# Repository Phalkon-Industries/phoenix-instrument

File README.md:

Git repo for the content of the new Phoenix ph handheld instrument.

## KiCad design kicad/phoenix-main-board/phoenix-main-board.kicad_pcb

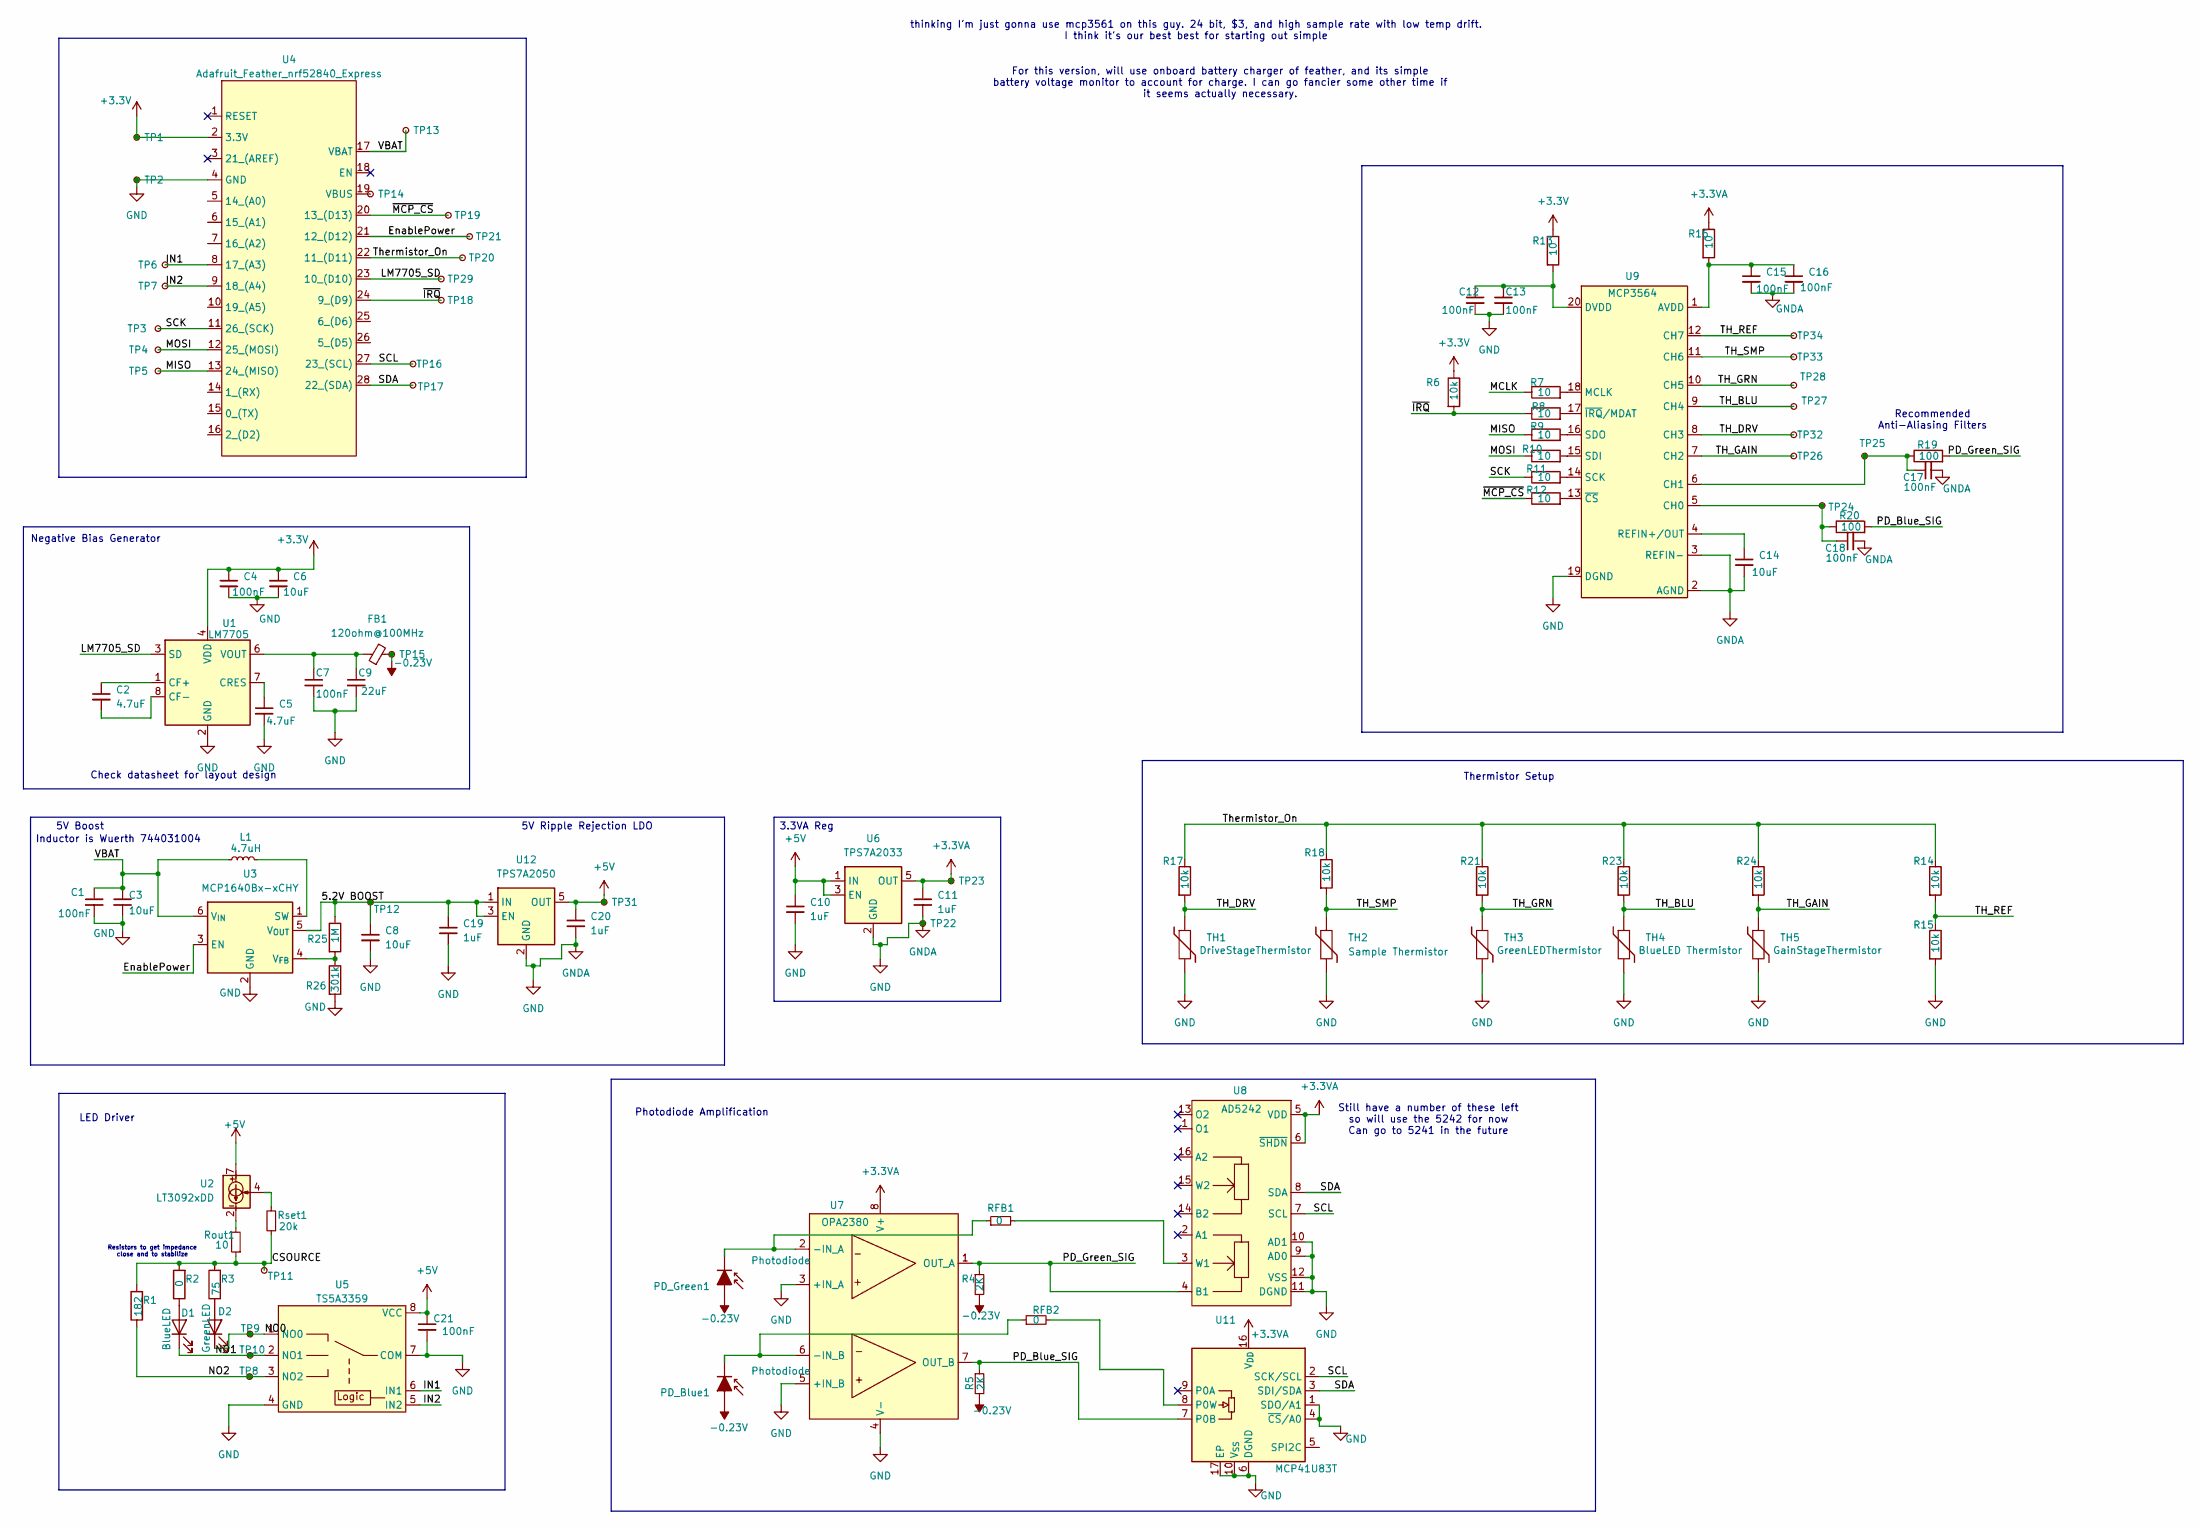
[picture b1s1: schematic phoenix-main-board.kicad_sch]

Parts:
C1, C4, C7, C12, C13, C15, C16, C17, C18, C21: 100nF; C_0603_1608Metric
C2, C5: 4.7uF; C_0603_1608Metric
C3, C6, C8, C14: 10uF; C_0603_1608Metric
C9: 22uF; C_0603_1608Metric
C10, C11, C19, C20: 1uF; C_0603_1608Metric
D1: BlueLED; LED_D5.0mm_Horizontal_O1.27mm_Z3.0mm
D2: GreenLED; LED_D5.0mm_Horizontal_O1.27mm_Z3.0mm
FB1: 120ohm@100MHz; R_0603_1608Metric
L1: 4.7uH; L_Wuerth_WE-TPC-3816
PD_Blue1: Photodiode; PD_Vertical
PD_Green1: Photodiode; PD_Vertical
R1: 182; R_0603_1608Metric
R2: 0; R_0603_1608Metric
R3: 75; R_0603_1608Metric
R4, R5: 2K; R_0603_1608Metric
R6, R14, R15, R17, R18, R21, R23, R24: 10k; R_0603_1608Metric
R7, R8, R9, R10, R11, R12, R13, R16: 10; R_0603_1608Metric
R19, R20: 100; R_0603_1608Metric
R25: 1M; R_0603_1608Metric
R26: 301k; R_0603_1608Metric
RFB1, RFB2: 0; R_0603_1608Metric
Rout1: 10; R_0603_1608Metric
Rset1: 20k; R_0603_1608Metric
TH1: DriveStageThermistor; R_0603_1608Metric
TH2: Sample Thermistor; ThermistorWire
TH3: GreenLEDThermistor; ThermistorWire
TH4: BlueLED Thermistor; ThermistorWire
TH5: GainStageThermistor; R_0603_1608Metric
TP1, TP2, TP3, TP4, TP5, TP6, TP7, TP8, TP9, TP10, TP11, TP12, TP13, TP14, TP15, TP16, TP17, TP18, TP19, TP20, TP21, TP22, TP23, TP24, TP25, TP26, TP27, TP28, TP29, TP31, TP32, TP33, TP34: TestPoint_Small; TestPoint_Keystone_5000-5004_Miniature
U1: LM7705; VSSOP-8_3x3mm_P0.65mm
U2: LT3092xDD; DFN-8-1EP_3x3mm_P0.5mm_EP1.66x2.38mm
U3: MCP1640Bx-xCHY; SOT-23-6
U4: Adafruit_Feather_nrf52840_Express; Adafruit Feather nrf52840 Express
U5: TS5A3359; VSSOP-8_2.3x2mm_P0.5mm
U6: TPS7A2033; SOT-23-5
U7: OPA2380; MSOP-8_3x3mm_P0.65mm
U8: AD5242; TSSOP-16_4.4x5mm_P0.65mm
U9: MCP3564; TSSOP-20_4.4x6.5mm_P0.65mm
U11: MCP41U83T; Texas_RSA_VQFN-16-1EP_4x4mm_P0.65mm_EP2.7x2.7mm
U12: TPS7A2050; SOT-23-5

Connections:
+3.3V: C4.1, C6.1, R6.1, R13.1, TP1.1, U1.4 (VDD), U4.2 (3.3V)
+3.3VA: C11.1, R16.1, TP23.1, U6.5 (OUT), U7.8 (V+), U8.5 (VDD), U8.6 (~SHDN), U11.16 (V_{DD})
+5V: C10.1, C20.1, C21.1, TP31.1, U2.7, U2.8, U5.8 (VCC), U6.1 (IN), U6.3 (EN), U12.5 (OUT)
-0.23V: FB1.2, PD_Blue1.2 (A), PD_Green1.2 (A), R4.2, R5.2, TP15.1
/5.2V BOOST: C8.1, C19.1, R25.1, TP12.1, U3.5 (V_{OUT}), U12.1 (IN), U12.3 (EN)
/CSOURCE: R1.2, R2.2, R3.2, Rout1.1, Rset1.1, TP11.1
/EnablePower: TP21.1, U3.3 (EN), U4.21 (12_(D12))
/IN1: TP6.1, U4.8 (17_(A3)), U5.6 (IN1)
/IN2: TP7.1, U4.9 (18_(A4)), U5.5 (IN2)
/LM7705_SD: TP29.1, U1.3 (SD), U4.23 (10_(D10))
/MCLK: R7.1
/MISO: R9.1, TP5.1, U4.13 (24_(MISO))
/MOSI: R10.1, TP4.1, U4.12 (25_(MOSI))
/NO0: D2.1 (K), TP9.1, U5.1 (NO0)
/NO1: D1.1 (K), TP10.1, U5.2 (NO1)
/NO2: R1.1, TP8.1, U5.3 (NO2)
/PD_Blue_SIG: R5.1, R20.2, U7.7 (OUT_B), U11.7 (P0B)
/PD_Green_SIG: R4.1, R19.2, U7.1 (OUT_A), U8.4 (B1)
/SCK: R11.1, TP3.1, U4.11 (26_(SCK))
/SCL: TP16.1, U4.27 (23_(SCL)), U8.7 (SCL), U11.2 (SCK/SCL)
/SDA: TP17.1, U4.28 (22_(SDA)), U8.8 (SDA), U11.3 (SDI/SDA)
/TH_BLU: R23.2, TH4.1, TP27.1, U9.9 (CH4)
/TH_DRV: R17.2, TH1.1, TP32.1, U9.8 (CH3)
/TH_GAIN: R24.2, TH5.1, TP26.1, U9.7 (CH2)
/TH_GRN: R21.2, TH3.1, TP28.1, U9.10 (CH5)
/TH_REF: R14.2, R15.1, TP34.1, U9.12 (CH7)
/TH_SMP: R18.2, TH2.1, TP33.1, U9.11 (CH6)
/Thermistor_On: R14.1, R17.1, R18.1, R21.1, R23.1, R24.1, TP20.1, U4.22 (11_(D11))
/VBAT: C1.1, C3.1, L1.1, TP13.1, U3.6 (V_{IN}), U4.17 (VBAT)
/~IRQ: R6.2, R8.1, TP18.1, U4.24 (9_(D9))
/~MCP_CS: R12.1, TP19.1, U4.20 (13_(D13))
GND: C1.2, C3.2, C4.2, C5.2, C6.2, C7.2, C8.2, C9.2, C10.2, C11.2, C12.2, C13.2, C14.2, C15.2, C16.2, C17.2, C18.2, C19.2, C20.2, C21.2, R15.2, R26.2, TH1.2, TH2.2, TH3.2, TH4.2, TH5.2, TP2.1, TP22.1, U1.2 (GND), U1.5 (GND), U3.2 (GND), U4.4 (GND), U5.4 (GND), U5.7 (COM), U6.2 (GND), U7.3 (+IN_A), U7.4 (V-), U7.5 (+IN_B), U8.9 (AD0), U8.10 (AD1), U8.11 (DGND), U8.12 (VSS), U9.2 (AGND), U9.3 (REFIN-), U9.19 (DGND), U11.1 (SDO/A1), U11.4 (~CS/A0), U11.6 (DGND), U11.10 (V_{SS}), U11.17 (EP), U12.2 (GND)
unnamed: D1.2 (A), R2.1
unnamed: D2.2 (A), R3.1
unnamed: PD_Blue1.1 (K), RFB2.1, U7.6 (-IN_B)
unnamed: PD_Green1.1 (K), RFB1.1, U7.2 (-IN_A)
unnamed: Rout1.2, U2.1, U2.2, U2.9
unnamed: Rset1.2, U2.4
unnamed: C2.1, U1.1 (CF+)
unnamed: C2.2, U1.8 (CF-)
unnamed: C5.1, U1.7 (CRES)
unnamed: C7.1, C9.1, FB1.1, U1.6 (VOUT)
unnamed: L1.2, U3.1 (SW)
unnamed: R25.2, R26.1, U3.4 (V_{FB})
unnamed: TP14.1, U4.19 (VBUS)
unnamed: RFB1.2, U8.3 (W1)
unnamed: C15.1, C16.1, R16.2, U9.1 (AVDD)
unnamed: C18.1, R20.1, TP24.1, U9.5 (CH0)
unnamed: C17.1, R19.1, TP25.1, U9.6 (CH1)
unnamed: C12.1, C13.1, R13.2, U9.20 (DVDD)
unnamed: R7.2, U9.18 (MCLK)
unnamed: C14.1, U9.4 (REFIN+/OUT)
unnamed: R11.2, U9.14 (SCK)
unnamed: R10.2, U9.15 (SDI)
unnamed: R9.2, U9.16 (SDO)
unnamed: R12.2, U9.13 (~CS)
unnamed: R8.2, U9.17 (~IRQ/MDAT)
unnamed: RFB2.2, U11.8 (P0W)

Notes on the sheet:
Inductor is Wuerth 744031004
For this version, will use onboard battery charger of feather, and its simple battery voltage monitor to account for charge. I can go fancier some other time if it seems actually necessary.
Check datasheet for layout design
Photodiode Amplification
3.3VA Reg
Resistors to get impedance close and to stabilize
Recommended Anti-Aliasing Filters
thinking I'm just gonna use mcp3561 on this guy. 24 bit, $3, and high sample rate with low temp drift. I think it's our best best for starting out simple
LED Driver
5V Boost
Negative Bias Generator
Thermistor Setup
5V Ripple Rejection LDO
Still have a number of these left so will use the 5242 for now Can go to 5241 in the future

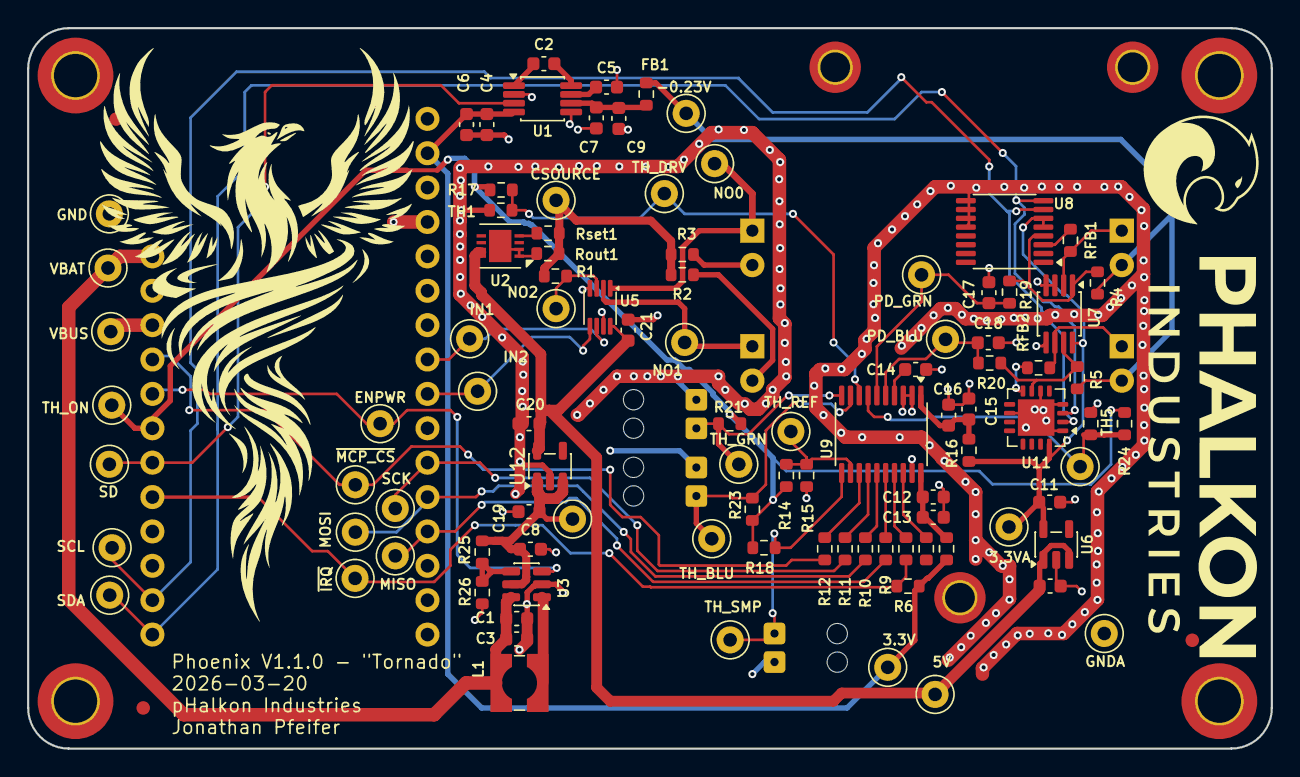
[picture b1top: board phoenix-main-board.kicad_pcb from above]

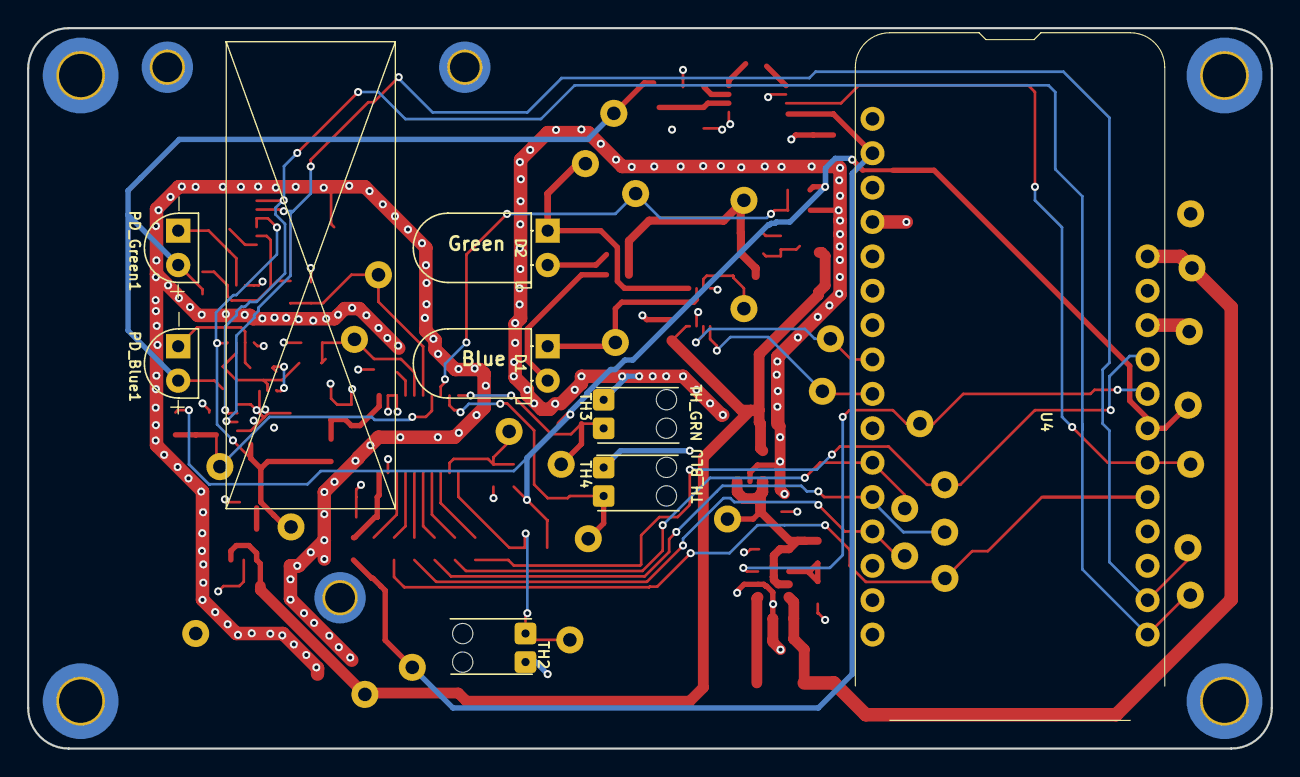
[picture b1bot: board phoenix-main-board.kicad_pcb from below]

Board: 4 copper layers, 91.9 x 53.2 mm, 108 parts (8 on the bottom side), 57 nets.

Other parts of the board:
FID1: Fiducial_1mm_Mask2mm
FID2, FID3: (no value)

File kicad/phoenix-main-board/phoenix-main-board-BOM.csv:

"Id";"Designator";"Footprint";"Quantity";"Designation";"Supplier and ref";
1;"TP25,TP11,TP31,TP7,TP2,TP16,TP23,TP22,TP9,TP33,TP14,TP15,TP5,TP3,TP1,TP26,TP34,TP10,TP4,TP19,TP18,TP32,TP29,TP27,TP17,TP20,TP8,TP24,TP6,TP12,TP28,TP21,TP13";"TestPoint_Keystone_5000-5004_Miniature";33;"TestPoint_Small";;;
2;"U11";"Texas_RSA_VQFN-16-1EP_4x4mm_P0.65mm_EP2.7x2.7mm";1;"MCP41U83T";;;
3;"R19,R20";"R_0603_1608Metric";2;"100";;;
4;"R7,R8,R10,R11,R12,Rout1,R13,R16,R9";"R_0603_1608Metric";9;"10";;;
5;"C12,C18,C7,C13,C16,C15,C21,C1,C17,C4";"C_0603_1608Metric";10;"100nF";;;
6;"C5,C2";"C_0603_1608Metric";2;"4.7uF";;;
7;"U1";"VSSOP-8_3x3mm_P0.65mm";1;"LM7705";;;
8;"U7";"MSOP-8_3x3mm_P0.65mm";1;"OPA2380";;;
9;"C6,C14,C8,C3";"C_0603_1608Metric";4;"10uF";;;
10;"FID3,FID2";"";2;"";;;
11;"R2,RFB2,RFB1";"R_0603_1608Metric";3;"0";;;
12;"Rset1";"R_0603_1608Metric";1;"20k";;;
13;"U2";"DFN-8-1EP_3x3mm_P0.5mm_EP1.66x2.38mm";1;"LT3092xDD";;;
14;"R5,R4";"R_0603_1608Metric";2;"2K";;;
15;"C9";"C_0603_1608Metric";1;"22uF";;;
16;"C11,C20,C10,C19";"C_0603_1608Metric";4;"1uF";;;
17;"U5";"VSSOP-8_2.3x2mm_P0.5mm";1;"TS5A3359";;;
18;"R3";"R_0603_1608Metric";1;"75";;;
19;"U9";"TSSOP-20_4.4x6.5mm_P0.65mm";1;"MCP3564";;;
20;"TH1";"R_0603_1608Metric";1;"DriveStageThermistor";;;
21;"R14,R24,R18,R23,R21,R17,R15,R6";"R_0603_1608Metric";8;"10k";;;
22;"U3";"SOT-23-6";1;"MCP1640Bx-xCHY";;;
23;"L1";"L_Wuerth_WE-TPC-3816";1;"4.7uH";;;
24;"R26";"R_0603_1608Metric";1;"301k";;;
25;"FID1";"Fiducial_1mm_Mask2mm";1;"Fiducial_1mm_Mask2mm";;;
26;"U12";"SOT-23-5";1;"TPS7A2050";;;
27;"TH5";"R_0603_1608Metric";1;"GainStageThermistor";;;
28;"U8";"TSSOP-16_4.4x5mm_P0.65mm";1;"AD5242";;;
29;"R1";"R_0603_1608Metric";1;"182";;;
30;"U6";"SOT-23-5";1;"TPS7A2033";;;
31;"R25";"R_0603_1608Metric";1;"1M";;;
32;"FB1";"R_0603_1608Metric";1;"120ohm@100MHz";;;
33;"TH4";"ThermistorWire";1;"BlueLED Thermistor";;;
34;"D2";"LED_D5.0mm_Horizontal_O1.27mm_Z3.0mm";1;"GreenLED";;;
35;"D1";"LED_D5.0mm_Horizontal_O1.27mm_Z3.0mm";1;"BlueLED";;;
36;"TH2";"ThermistorWire";1;"Sample Thermistor";;;
37;"U4";"Adafruit Feather nrf52840 Express";1;"Adafruit_Feather_nrf52840_Express";;;
38;"PD_Green1,PD_Blue1";"PD_Vertical";2;"Photodiode";;;
39;"TH3";"ThermistorWire";1;"GreenLEDThermistor";;;

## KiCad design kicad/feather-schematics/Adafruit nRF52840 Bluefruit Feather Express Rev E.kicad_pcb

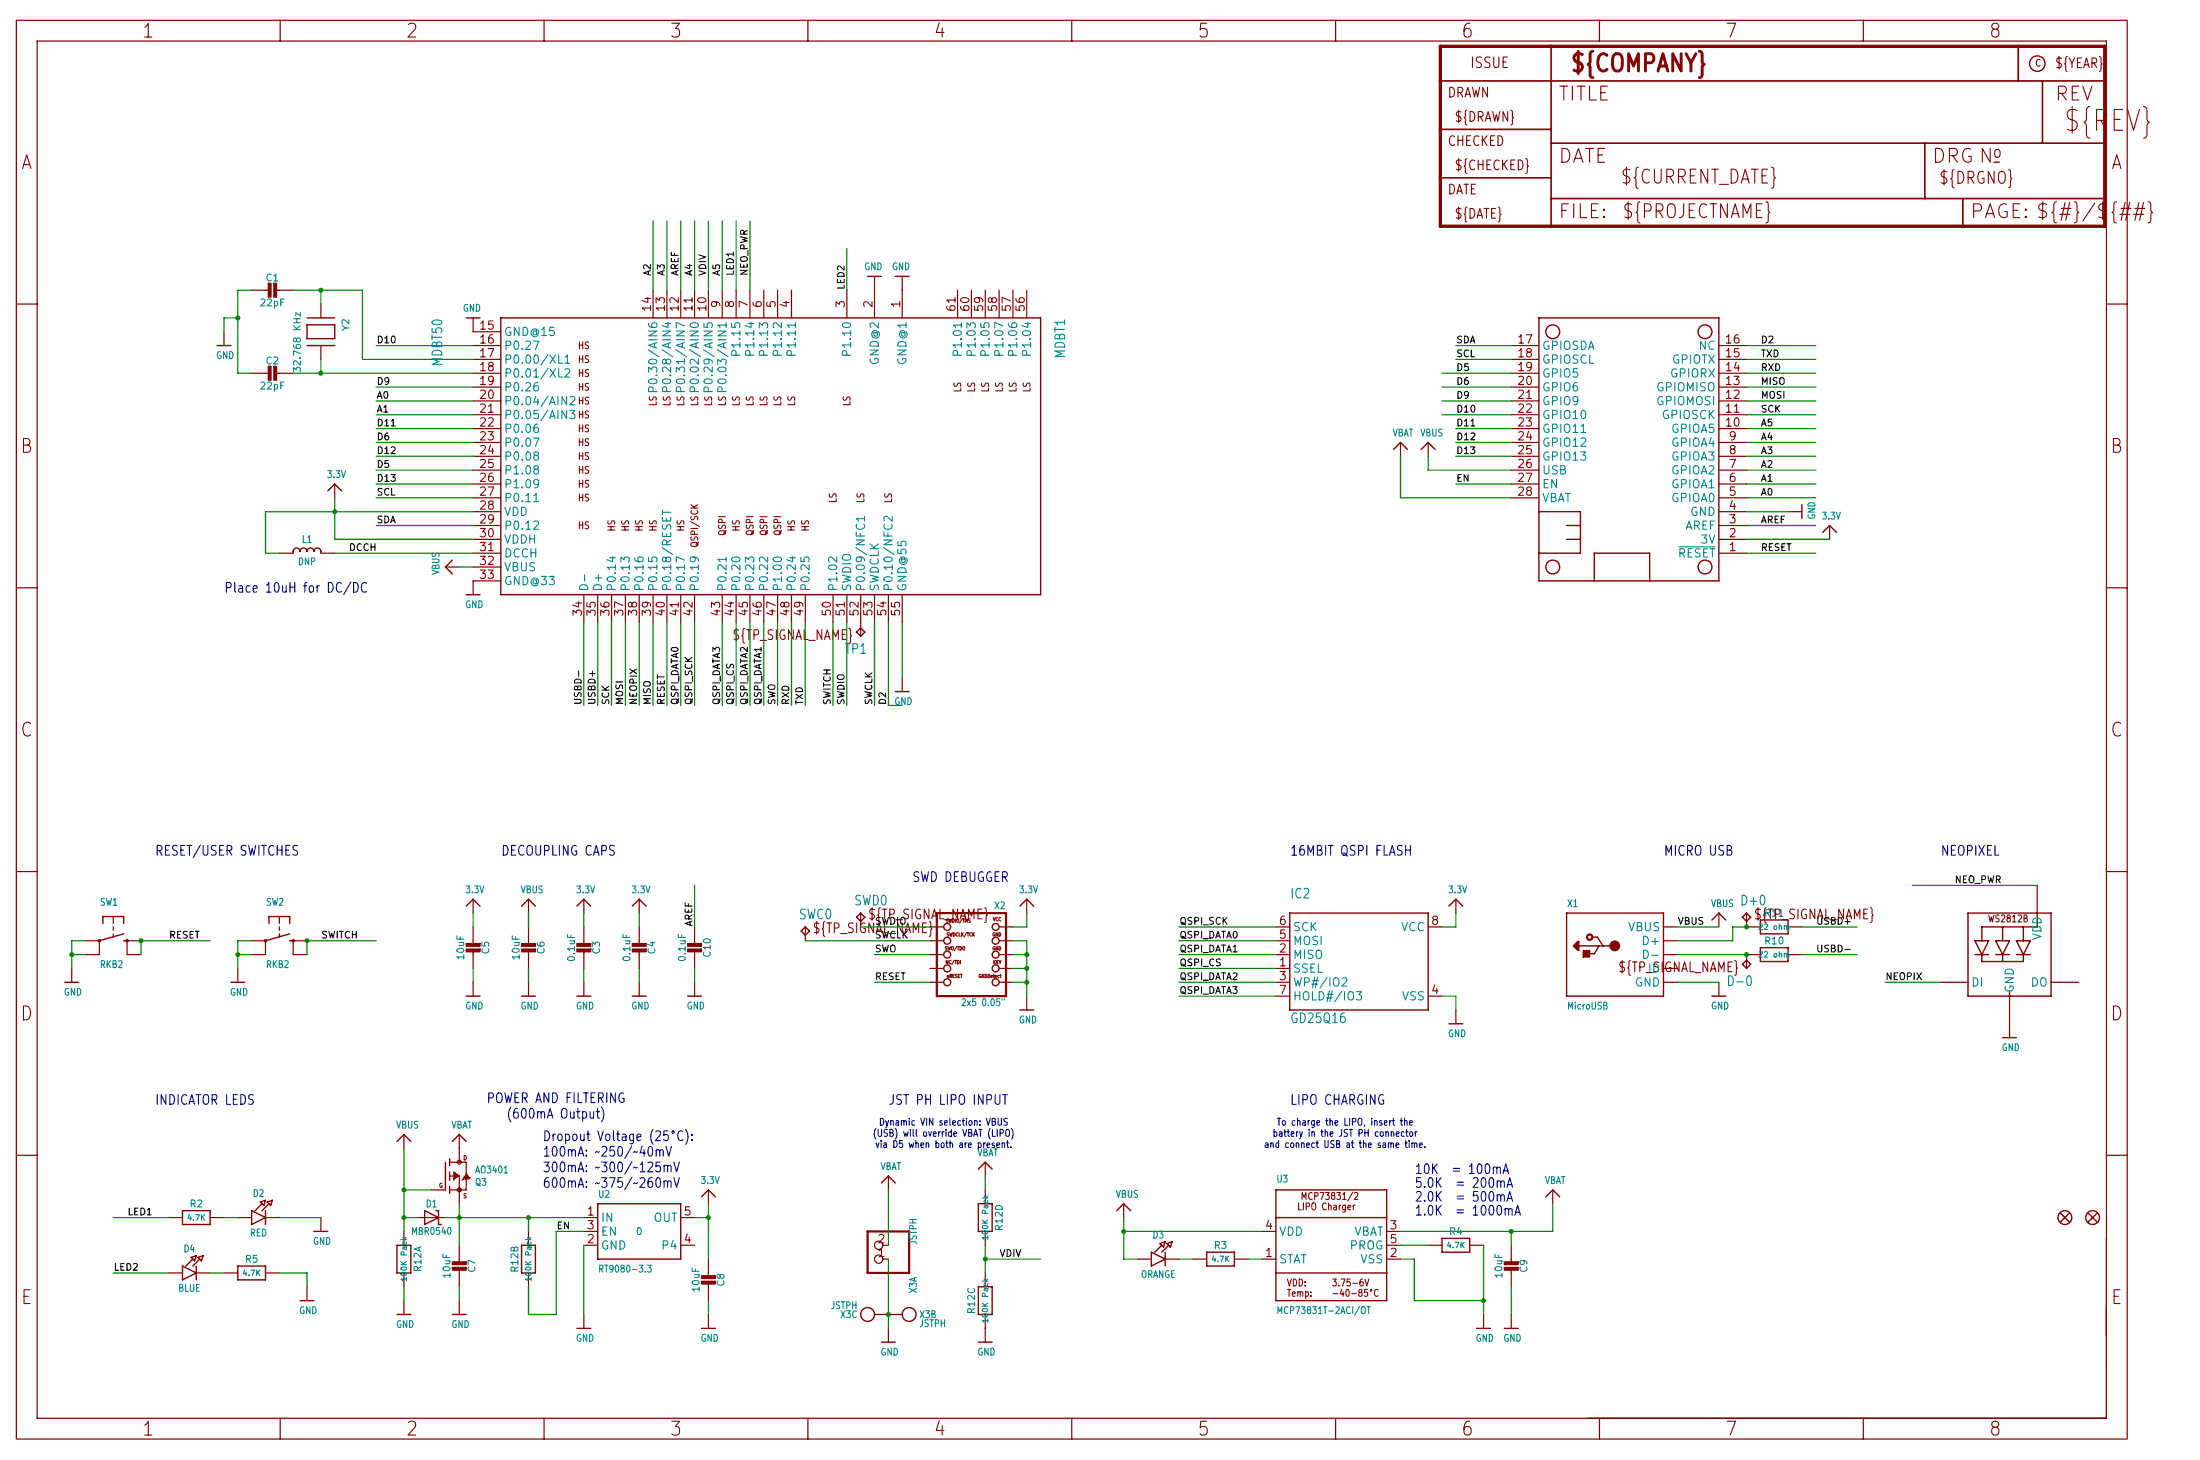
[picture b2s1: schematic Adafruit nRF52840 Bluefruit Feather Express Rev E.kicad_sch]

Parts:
C1, C2: 22pF; 0603-NO
C3, C4, C10: 0.1uF; 0603-NO
C5, C6, C7, C8, C9: 10uF; 0805-NO
D1: MBR0540; SOD-123
D2: RED; CHIPLED_0603_NOOUTLINE
D3: ORANGE; CHIPLED_0603_NOOUTLINE
D4: BLUE; CHIPLED_0603_NOOUTLINE
D+0: TPTP10R; TP10R
D-0: TPTP10R; TP10R
FID1, FID2: FIDUCIAL_1MM
IC2: GD25Q16; USON8
L1: DNP; _0805MP
LED1: WS2812B_3535FULL; LED3535_FULLPADS
MDBT1: MDBT50
MS1: FEATHERWING_NODIM
Q3: AO3401; SOT23-R
R2, R3, R4, R5: 4.7K; 0603-NO
R10, R11: 22 ohm; _0603MP
R12: 100K Pack; RESPACK_4X0603
SW1, SW2: RKB2; BTN_RKB2_4.6X2.8
SWC0: TPTP12R; TP12R
SWD0: TPTP12R; TP12R
TP1: TPTP10R; TP10R
U2: RT9080-3.3; SOT23-5; JLC_ROTATION 0
U3: MCP73831T-2ACI/OT; SOT23-5
X1: MicroUSB; 4UCONN_20329_V2
X2: 2x5 0.05"; 2X05_1.27MM_BOX_POSTS
X3: JSTPH; JSTPH2_BATT
Y2: 32.768 KHz; XTAL3215

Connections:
3.3V: C3.2, C4.2, C5.2, C8.2, IC2.8 (VCC), L1.1, MDBT1.28 (VDD), MDBT1.30 (VDDH), MS1.2 (3V), U2.5 (OUT), X2.1 (VCC)
A0: MDBT1.20 (P0.04/AIN2), MS1.5 (GPIOA0)
A1: MDBT1.21 (P0.05/AIN3), MS1.6 (GPIOA1)
A2: MDBT1.14 (P0.30/AIN6), MS1.7 (GPIOA2)
A3: MDBT1.13 (P0.28/AIN4), MS1.8 (GPIOA3)
A4: MDBT1.11 (P0.02/AIN0), MS1.9 (GPIOA4)
A5: MDBT1.9 (P0.03/AIN1), MS1.10 (GPIOA5)
AREF: C10.2, MDBT1.12 (P0.31/AIN7), MS1.3 (AREF)
D2: MDBT1.54 (P0.10/NFC2), MS1.16 (NC)
D5: MDBT1.25 (P1.08), MS1.19 (GPIO5)
D6: MDBT1.23 (P0.07), MS1.20 (GPIO6)
D9: MDBT1.19 (P0.26), MS1.21 (GPIO9)
D10: MDBT1.16 (P0.27), MS1.22 (GPIO10)
D11: MDBT1.22 (P0.06), MS1.23 (GPIO11)
D12: MDBT1.24 (P0.08), MS1.24 (GPIO12)
D13: MDBT1.26 (P1.09), MS1.25 (GPIO13)
D+: D+0.TP, R11.1, X1.D+
D-: D-0.TP, R10.1, X1.D-
DCCH: L1.2, MDBT1.31 (DCCH)
EN: MS1.27 (EN), R12.2 (1), U2.3 (EN)
GND: C1.2, C2.2, C3.1, C4.1, C5.1, C6.1, C7.1, C8.1, C9.1, C10.1, D2.C, IC2.4 (VSS), LED1.4 (GND), MDBT1.1 (GND@1), MDBT1.2 (GND@2), MDBT1.15 (GND@15), MDBT1.33 (GND@33), MDBT1.55 (GND@55), MS1.4 (GND), R4.2, R5.2, R12.3 (1), R12.8 (2), SW1.A, SW1.A' (P1), SW2.A, SW2.A' (P1), U2.2 (GND), U3.2 (VSS), X1.BASE@1 (GND), X1.BASE@2 (GND), X1.GND, X1.SPRT@1 (GND), X1.SPRT@2 (GND), X1.SPRT@3 (GND), X1.SPRT@4 (GND), X2.3 (GND@1), X2.5 (GND@2), X2.7 (KEY), X2.9 (GNDDETECT), X3.1, X3.NC1, X3.NC2
LED1: MDBT1.8 (P1.15), R2.1
LED2: D4.A, MDBT1.3 (P1.10)
MISO: MDBT1.39 (P0.15), MS1.13 (GPIOMISO)
MOSI: MDBT1.37 (P0.13), MS1.12 (GPIOMOSI)
unnamed: D3.C, R3.1
unnamed: D2.A, R2.2
unnamed: C1.1, MDBT1.17 (P0.00/XL1), Y2.P$1
unnamed: C2.1, MDBT1.18 (P0.01/XL2), Y2.P$2
unnamed: R3.2, U3.1 (STAT)
unnamed: R4.1, U3.5 (PROG)
unnamed: D4.C, R5.1
NEOPIX: LED1.1 (DI), MDBT1.38 (P0.16)
NEO_PWR: LED1.2 (VDD), MDBT1.7 (P1.14)
NFC2: MDBT1.52 (P0.09/NFC1), TP1.TP
QSPI_CS: IC2.1 (SSEL), MDBT1.44 (P0.20)
QSPI_DATA0: IC2.5 (MOSI), MDBT1.41 (P0.17)
QSPI_DATA1: IC2.2 (MISO), MDBT1.46 (P0.22)
QSPI_DATA2: IC2.3 (WP#/IO2), MDBT1.45 (P0.23)
QSPI_DATA3: IC2.7 (HOLD#/IO3), MDBT1.43 (P0.21)
QSPI_SCK: IC2.6 (SCK), MDBT1.42 (P0.19)
RESET: MDBT1.40 (P0.18/RESET), MS1.1 (~RESET), SW1.B (S), SW1.B' (S1), X2.10 (NRESET)
RXD: MDBT1.48 (P0.24), MS1.14 (GPIORX)
SCK: MDBT1.36 (P0.14), MS1.11 (GPIOSCK)
SCL: MDBT1.27 (P0.11), MS1.18 (GPIOSCL)
SDA: MDBT1.29 (P0.12), MS1.17 (GPIOSDA)
SWCLK: MDBT1.53 (SWDCLK), SWC0.TP, X2.4 (SWDCLK)
SWDIO: MDBT1.51 (SWDIO), SWD0.TP, X2.2 (SWDIO)
SWITCH: MDBT1.50 (P1.02), SW2.B (S), SW2.B' (S1)
SWO: MDBT1.47 (P1.00), X2.6 (SWO)
TXD: MDBT1.49 (P0.25), MS1.15 (GPIOTX)
USBD+: MDBT1.35 (D+), R11.2
USBD-: MDBT1.34 (D-), R10.2
VBAT: C9.2, MS1.28 (VBAT), Q3.3 (D), R12.4 (1), U3.3 (VBAT), X3.2
VBUS: C6.2, D1.A, D3.A, MDBT1.32 (VBUS), MS1.26 (USB), Q3.1 (G), R12.1, U3.4 (VDD), X1.VBUS
VDIV: MDBT1.10 (P0.29/AIN5), R12.5 (2), R12.6 (2)
VHI: C7.2, D1.C, Q3.2 (S), R12.7 (2), U2.1 (IN)

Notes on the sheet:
To charge the LIPO, insert the battery in the JST PH connector and connect USB at the same time.
16MBIT QSPI FLASH
Dynamic VIN selection: VBUS (USB) will override VBAT (LIPO) via D5 when both are present.
Dropout Voltage (25°C): 100mA: ~250/~40mV 300mA: ~300/~125mV 600mA: ~375/~260mV
1.0K = 1000mA
MICRO USB
DECOUPLING CAPS
RESET/USER SWITCHES
INDICATOR LEDS
JST PH LIPO INPUT
POWER AND FILTERING (600mA Output)
SWD DEBUGGER
2.0K = 500mA
NEOPIXEL
Place 10uH for DC/DC
10K = 100mA
LIPO CHARGING
5.0K = 200mA

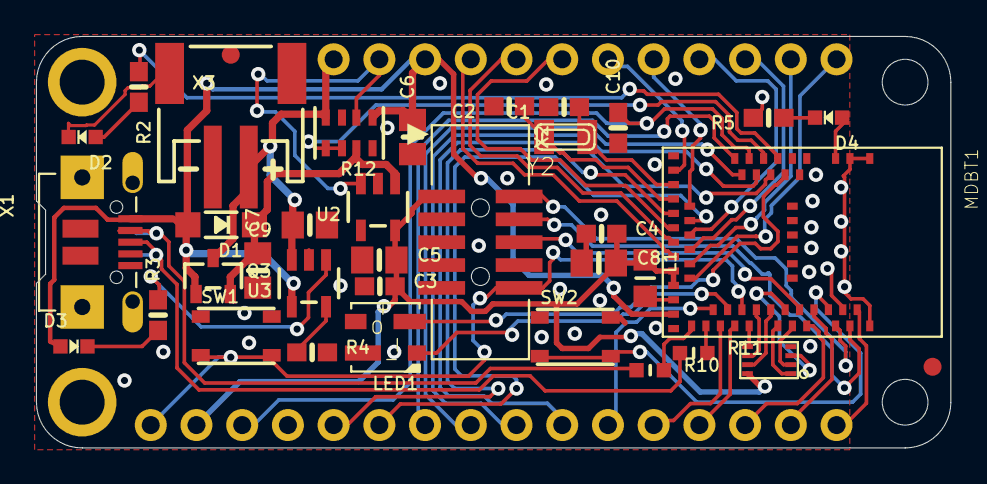
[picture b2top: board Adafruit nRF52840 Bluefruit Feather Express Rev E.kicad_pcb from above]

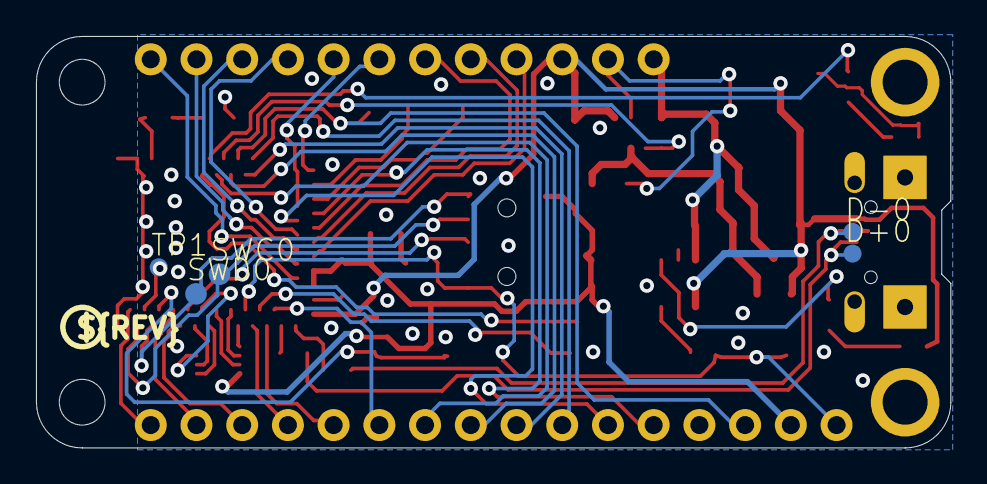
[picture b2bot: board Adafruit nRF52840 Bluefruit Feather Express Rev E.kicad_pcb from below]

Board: 2 copper layers, 50.8 x 22.9 mm, 45 parts (7 on the bottom side), 57 nets.

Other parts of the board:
U$10: PCBFEAT-REV-056
U$12: NRF52840_BOT
U$14: NRF52840_TOP

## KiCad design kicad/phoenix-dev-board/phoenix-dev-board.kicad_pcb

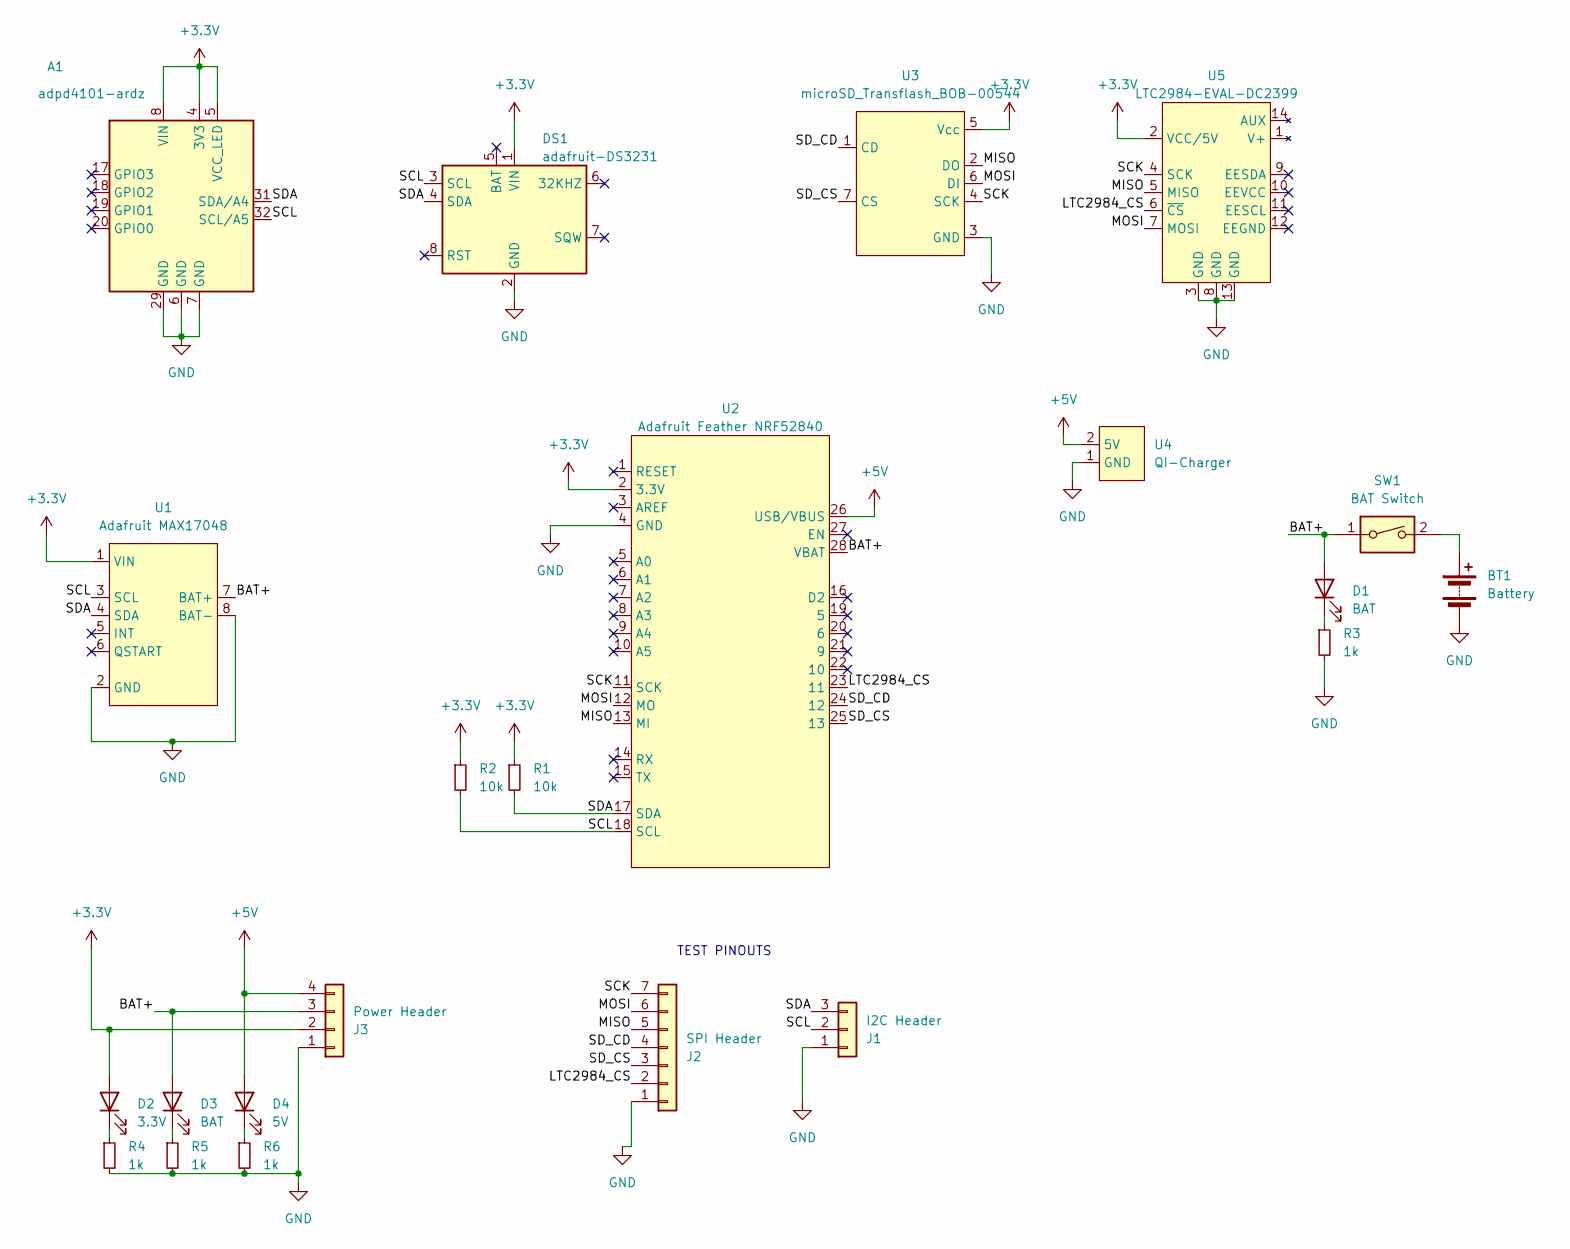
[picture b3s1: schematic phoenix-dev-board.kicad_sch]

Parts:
A1: adpd4101-ardz; adpda4101-ardz
BT1: Battery; JST_PH_S2B-PH-K_1x02_P2.00mm_Horizontal
D1, D3: BAT; LED_D3.0mm
D2: 3.3V; LED_D3.0mm
D4: 5V; LED_D3.0mm
DS1: adafruit-DS3231; adafruit-ds3231
J1: I2C Header; PinHeader_1x03_P2.54mm_Vertical
J2: SPI Header; PinHeader_1x07_P2.54mm_Vertical
J3: Power Header; PinHeader_1x04_P2.54mm_Vertical
R1, R2: 10k; R_Axial_DIN0204_L3.6mm_D1.6mm_P1.90mm_Vertical
R3, R4, R5, R6: 1k; R_Axial_DIN0204_L3.6mm_D1.6mm_P1.90mm_Vertical
SW1: BAT Switch; switch-GF-123-0054-CW_Industries
U1: Adafruit MAX17048; adafruit-max17048
U2: Adafruit Feather NRF52840; adafruit-nrf52840-feather-express
U3: microSD_Transflash_BOB-00544; microSD Transflash BOB-00544
U4: QI-Charger; PinHeader_1x02_P2.54mm_Vertical
U5: LTC2984-EVAL-DC2399; ltc2984-eval-dc2399

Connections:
+3.3V: A1.4 (3V3), A1.5 (VCC_LED), A1.8 (VIN), D2.2 (A), DS1.1 (VIN), J3.2, R1.1, R2.1, U1.1 (VIN), U2.2 (3.3V), U3.5 (Vcc), U5.2 (VCC/5V)
+5V: D4.2 (A), J3.4, U2.26 (USB/VBUS), U4.2 (5V)
/BAT+: D1.2 (A), D3.2 (A), J3.3, SW1.1, U1.7 (BAT+), U2.28 (VBAT)
/LTC2984_CS: J2.2, U2.23 (11), U5.6 (~CS)
/MISO: J2.5, U2.13 (MI), U3.2 (DO), U5.5 (MISO)
/MOSI: J2.6, U2.12 (MO), U3.6 (DI), U5.7 (MOSI)
/SCK: J2.7, U2.11 (SCK), U3.4 (SCK), U5.4 (SCK)
/SCL: A1.32 (SCL/A5), DS1.3 (SCL), J1.2, R2.2, U1.3 (SCL), U2.18 (SCL)
/SDA: A1.31 (SDA/A4), DS1.4 (SDA), J1.3, R1.2, U1.4 (SDA), U2.17 (SDA)
/SD_CD: J2.4, U2.24 (12), U3.1 (CD)
/SD_CS: J2.3, U2.25 (13), U3.7 (CS)
GND: A1.6 (GND), A1.7 (GND), A1.29 (GND), BT1.2 (-), DS1.2 (GND), J1.1, J2.1, J3.1, R3.2, R4.2, R5.2, R6.2, U1.2 (GND), U1.8 (BAT-), U2.4 (GND), U3.3 (GND), U4.1 (GND), U5.3 (GND), U5.8 (GND), U5.13 (GND)
unnamed: BT1.1 (+), SW1.2
unnamed: D1.1 (K), R3.1
unnamed: D2.1 (K), R4.1
unnamed: D3.1 (K), R5.1
unnamed: D4.1 (K), R6.1

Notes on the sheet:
TEST PINOUTS

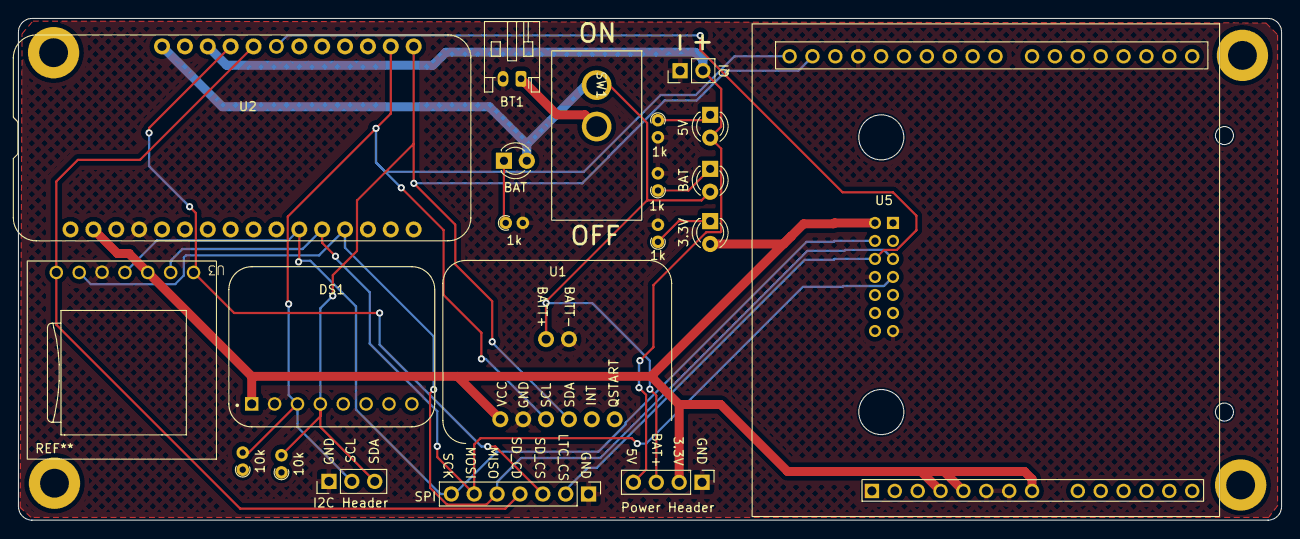
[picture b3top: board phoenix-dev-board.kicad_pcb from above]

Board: 2 copper layers, 140.2 x 55.7 mm, 22 parts (0 on the bottom side), 17 nets.
